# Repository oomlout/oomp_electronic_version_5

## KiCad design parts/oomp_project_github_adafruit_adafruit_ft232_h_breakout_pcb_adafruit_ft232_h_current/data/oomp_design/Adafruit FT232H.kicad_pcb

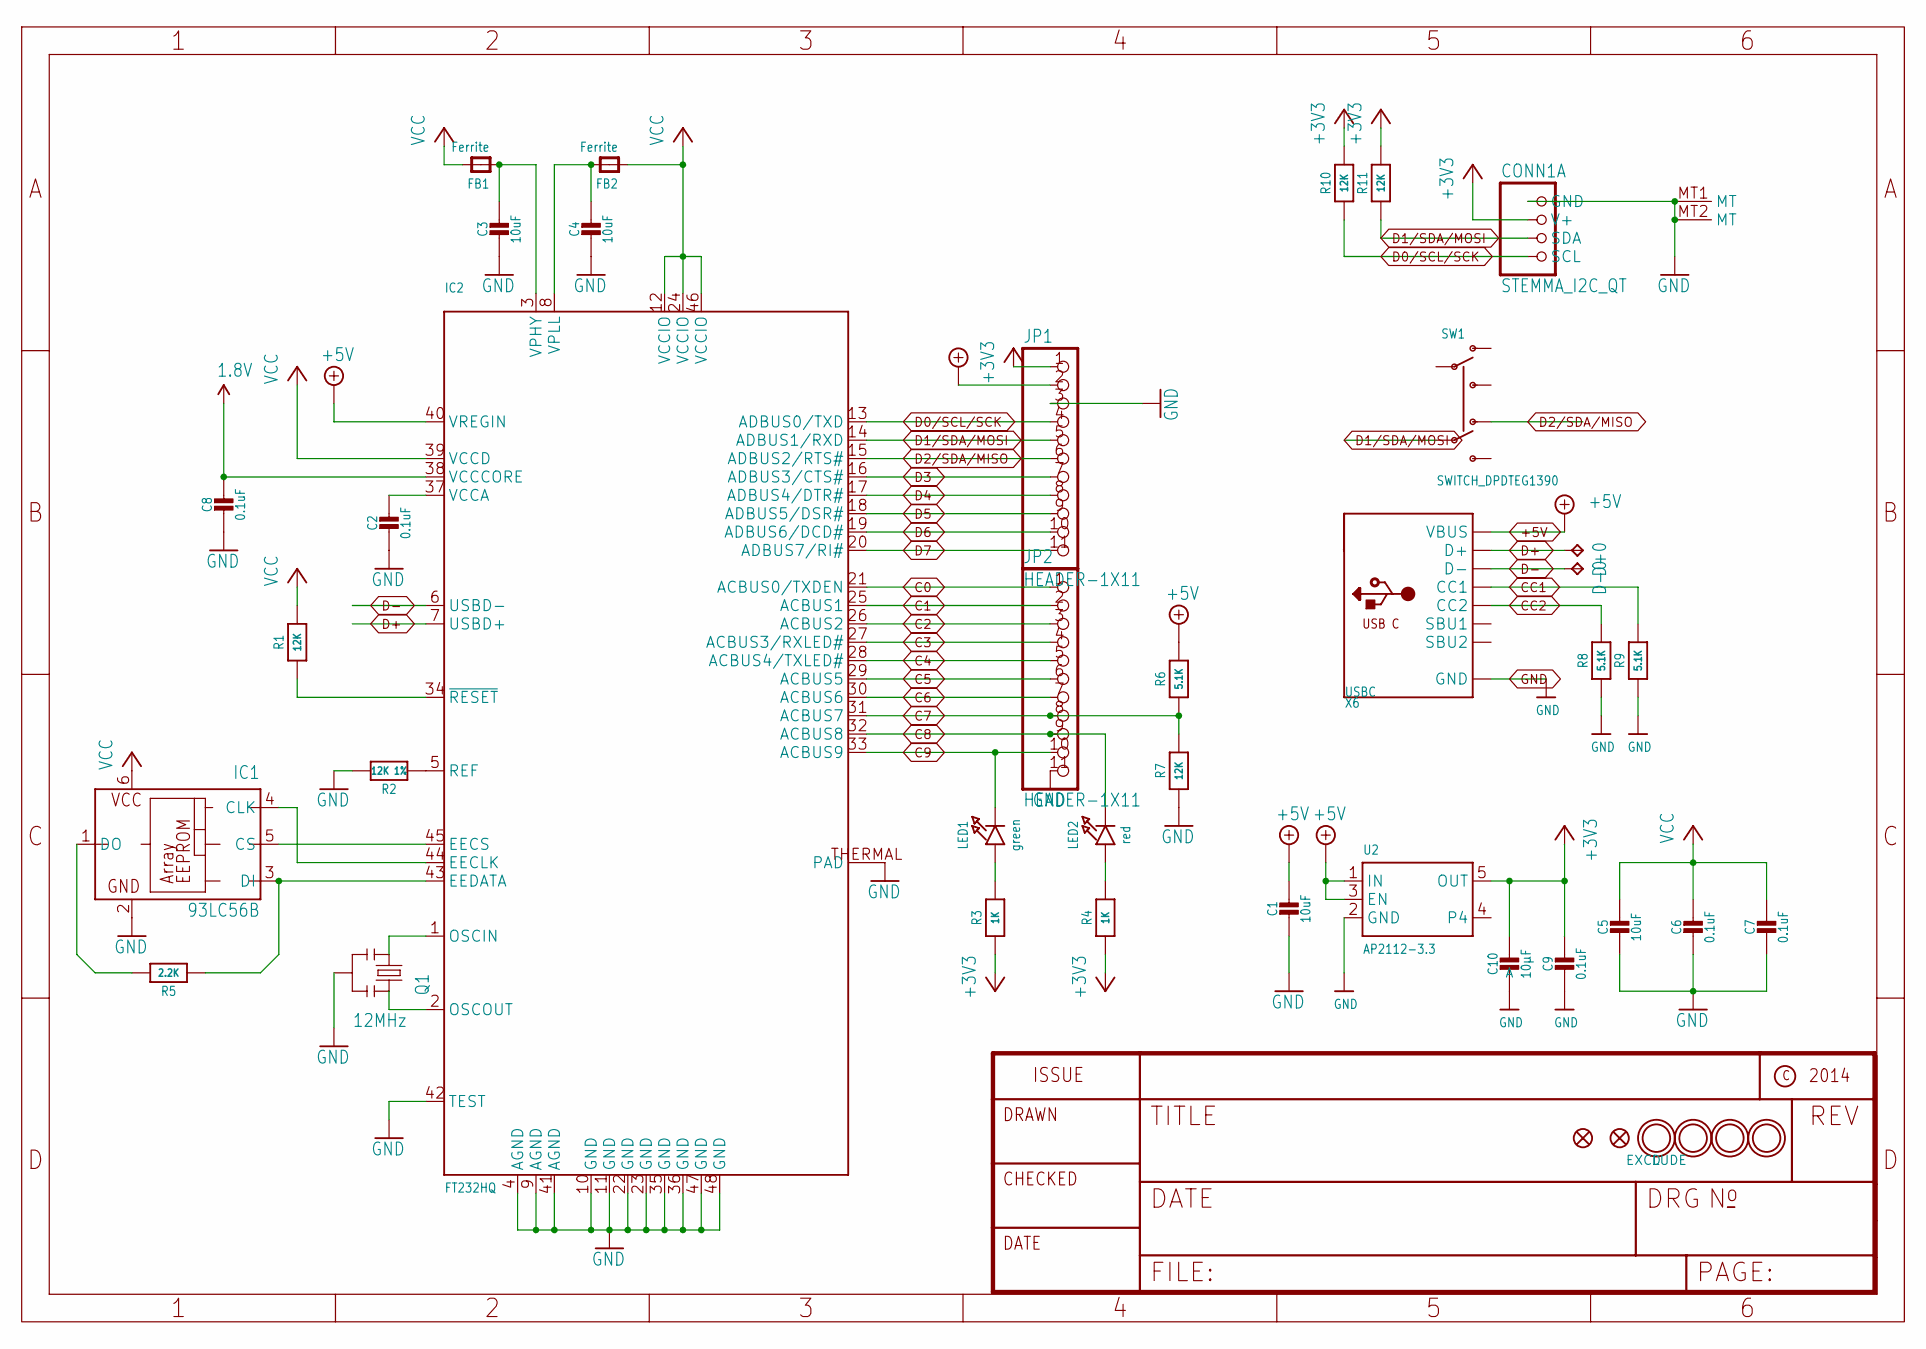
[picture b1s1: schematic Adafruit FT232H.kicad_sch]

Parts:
C1, C3, C4, C5: 10uF; 0805-NO
C2, C6, C7, C8, C9: 0.1uF; 0603-NO
C10: 10µF; 0805-NO
CONN1: STEMMA_I2C_QT; JST_SH4
D+0: TPTP17R; TP17R
D-0: TPTP17R; TP17R
FB1, FB2: Ferrite; _0805
FID1, FID2: FIDUCIAL""; FIDUCIAL_1MM
IC1: 93LC56B; SOT23-6; MPN 93LC76AT-I/OT
IC2: FT232HQ; QFN48_8MM
JP1, JP2: HEADER-1X11; 1X11_ROUND
LED1: green; CHIPLED_0805_NOOUTLINE
LED2: red; CHIPLED_0805_NOOUTLINE
Q1: 12MHz; RESONATOR-SMD
R1, R7, R10, R11: 12K; 0603-NO
R2: 12K 1%; 0603-NO
R3, R4: 1K; 0603-NO
R5: 2.2K; 0603-NO
R6, R8, R9: 5.1K; 0603-NO
SW1: SWITCH_DPDTEG1390; EG1390
U2: AP2112-3.3; SOT23-5
U$4, U$5, U$6, U$7: MOUNTINGHOLE2.5; MOUNTINGHOLE_2.5_PLATED
X6: USBC; USB_C_CUSB31-CFM2AX-01-X

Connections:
1.8V: C8.1, IC2.38 (VCCCORE)
+3V3: C9.1, C10.1, CONN1.2 (V+), JP1.1, R3.1, R4.1, R10.2, R11.2, U2.5 (OUT)
+5V: C1.1, IC2.40 (VREGIN), JP1.2, R6.2, U2.1 (IN), U2.3 (EN), X6.A4B9 (VBUS), X6.B4A9 (VBUS)
C0: IC2.21 (ACBUS0/TXDEN), JP2.1
C1: IC2.25 (ACBUS1), JP2.2
C2: IC2.26 (ACBUS2), JP2.3
C3: IC2.27 (ACBUS3/RXLED#), JP2.4
C4: IC2.28 (ACBUS4/TXLED#), JP2.5
C5: IC2.29 (ACBUS5), JP2.6
C6: IC2.30 (ACBUS6), JP2.7
C7: IC2.31 (ACBUS7), JP2.8, R6.1, R7.2
C8: IC2.32 (ACBUS8), JP2.9, LED2.C
C9: IC2.33 (ACBUS9), JP2.10, LED1.C
CC1: R9.2, X6.A5 (CC1)
CC2: R8.2, X6.B5 (CC2)
D0/SCL/SCK: CONN1.4 (SCL), IC2.13 (ADBUS0/TXD), JP1.4, R10.1
D1/SDA/MOSI: CONN1.3 (SDA), IC2.14 (ADBUS1/RXD), JP1.5, R11.1, SW1.P2
D2/SDA/MISO: IC2.15 (ADBUS2/RTS#), JP1.6, SW1.O2
D3: IC2.16 (ADBUS3/CTS#), JP1.7
D4: IC2.17 (ADBUS4/DTR#), JP1.8
D5: IC2.18 (ADBUS5/DSR#), JP1.9
D6: IC2.19 (ADBUS6/DCD#), JP1.10
D7: IC2.20 (ADBUS7/RI#), JP1.11
D+: D+0.TP, IC2.7 (USBD+), X6.A6 (D+), X6.B6 (D+)
D-: D-0.TP, IC2.6 (USBD-), X6.A7 (D-), X6.B7 (D-)
GND: C1.2, C2.2, C3.2, C4.2, C5.2, C6.2, C7.2, C8.2, C9.2, C10.2, CONN1.1 (GND), CONN1.MT1 (MT), CONN1.MT2 (MT), IC1.2 (GND), IC2.4 (AGND), IC2.9 (AGND), IC2.10 (GND), IC2.11 (GND), IC2.22 (GND), IC2.23 (GND), IC2.35 (GND), IC2.36 (GND), IC2.41 (AGND), IC2.42 (TEST), IC2.47 (GND), IC2.48 (GND), IC2.THERMAL (PAD), JP1.3, JP2.11, Q1.2, R2.2, R7.1, R8.1, R9.1, U2.2 (GND), X6.A1B12 (GND), X6.B1A12 (GND)
unnamed: IC2.1 (OSCIN), Q1.1
unnamed: IC2.2 (OSCOUT), Q1.3
unnamed: IC2.5 (REF), R2.1
unnamed: LED2.A, R4.2
unnamed: IC2.34 (~RESET), R1.1
unnamed: LED1.A, R3.2
unnamed: IC1.3 (DI), IC2.43 (EEDATA), R5.1
unnamed: IC1.5 (CS), IC2.45 (EECS)
unnamed: IC1.4 (CLK), IC2.44 (EECLK)
unnamed: IC1.1 (DO), R5.2
VCC: C5.1, C6.1, C7.1, FB1.2, FB2.1, IC1.6 (VCC), IC2.12 (VCCIO), IC2.24 (VCCIO), IC2.39 (VCCD), IC2.46 (VCCIO), R1.2
VCCA: C2.1, IC2.37 (VCCA)
VPHY: C3.1, FB1.1, IC2.3 (VPHY)
VPLL: C4.1, FB2.2, IC2.8 (VPLL)

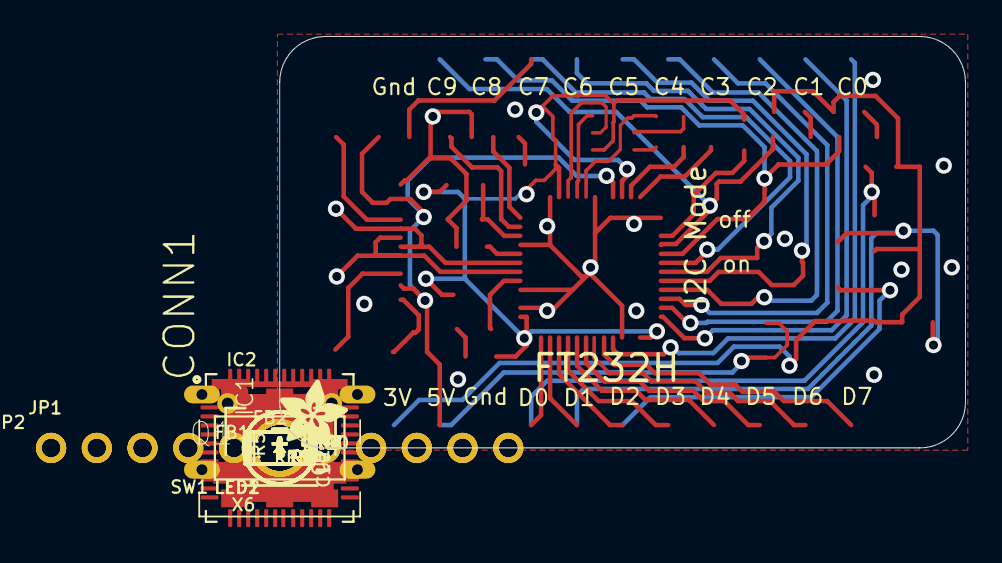
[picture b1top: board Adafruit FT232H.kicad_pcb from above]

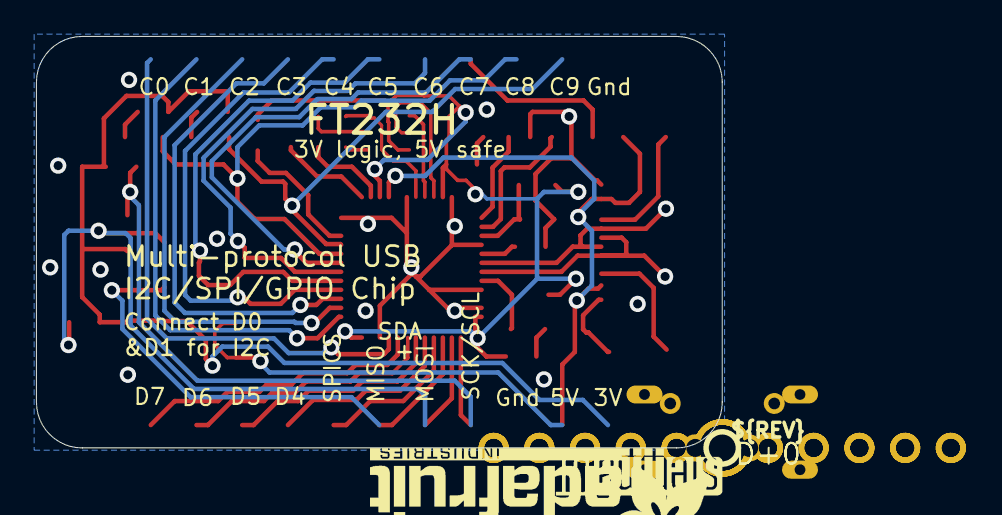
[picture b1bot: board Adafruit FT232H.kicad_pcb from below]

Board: 2 copper layers, 38.1 x 22.9 mm, 46 parts (5 on the bottom side), 40 nets.

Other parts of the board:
U$2: ADAFRUIT_3.5MM
U$3: ADAFRUIT_TEXT_20MM
U$8: STEMMAQT
U$11: PCBFEAT-REV-040

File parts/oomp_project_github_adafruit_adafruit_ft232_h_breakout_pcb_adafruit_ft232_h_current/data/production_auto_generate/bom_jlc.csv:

Comment,Designator,Footprint,LCSC Part #
,"JP1,JP2",Adafruit FT232H-import-fps:1X11_ROUND,C2894934
,U$2,Adafruit FT232H-import-fps:ADAFRUIT_3.5MM,
,U$3,Adafruit FT232H-import-fps:ADAFRUIT_TEXT_20MM,
,SW1,Adafruit FT232H-import-fps:EG1390,
,U$11,Adafruit FT232H-import-fps:PCBFEAT-REV-040,
,U$8,Adafruit FT232H-import-fps:STEMMAQT,
0.1uF,"C2,C6,C7,C8,C9",Adafruit FT232H-import-fps:0603-NO,C14663
10uF,"C1,C3,C4,C5",Adafruit FT232H-import-fps:0805-NO,
10µF,C10,Adafruit FT232H-import-fps:0805-NO,
12K,"R1,R7,R10,R11",Adafruit FT232H-import-fps:0603-NO,C2906989
12K 1%,R2,Adafruit FT232H-import-fps:0603-NO,C2906989
12MHz,Q1,Adafruit FT232H-import-fps:RESONATOR-SMD,
1K,"R3,R4",Adafruit FT232H-import-fps:0603-NO,C2907002
2.2K,R5,Adafruit FT232H-import-fps:0603-NO,C4190
5.1K,"R6,R8,R9",Adafruit FT232H-import-fps:0603-NO,C23186
93LC56B,IC1,Adafruit FT232H-import-fps:SOT23-6,
AP2112-3.3,U2,Adafruit FT232H-import-fps:SOT23-5,
Ferrite,"FB1,FB2",Adafruit FT232H-import-fps:_0805,
FT232HQ,IC2,Adafruit FT232H-import-fps:QFN48_8MM,
green,LED1,Adafruit FT232H-import-fps:CHIPLED_0805_NOOUTLINE,
red,LED2,Adafruit FT232H-import-fps:CHIPLED_0805_NOOUTLINE,
STEMMA_I2C_QT,CONN1,Adafruit FT232H-import-fps:JST_SH4,C160404
TPTP17R,"D+0,D-0",Adafruit FT232H-import-fps:TP17R,
USBC,X6,Adafruit FT232H-import-fps:USB_C_CUSB31-CFM2AX-01-X,

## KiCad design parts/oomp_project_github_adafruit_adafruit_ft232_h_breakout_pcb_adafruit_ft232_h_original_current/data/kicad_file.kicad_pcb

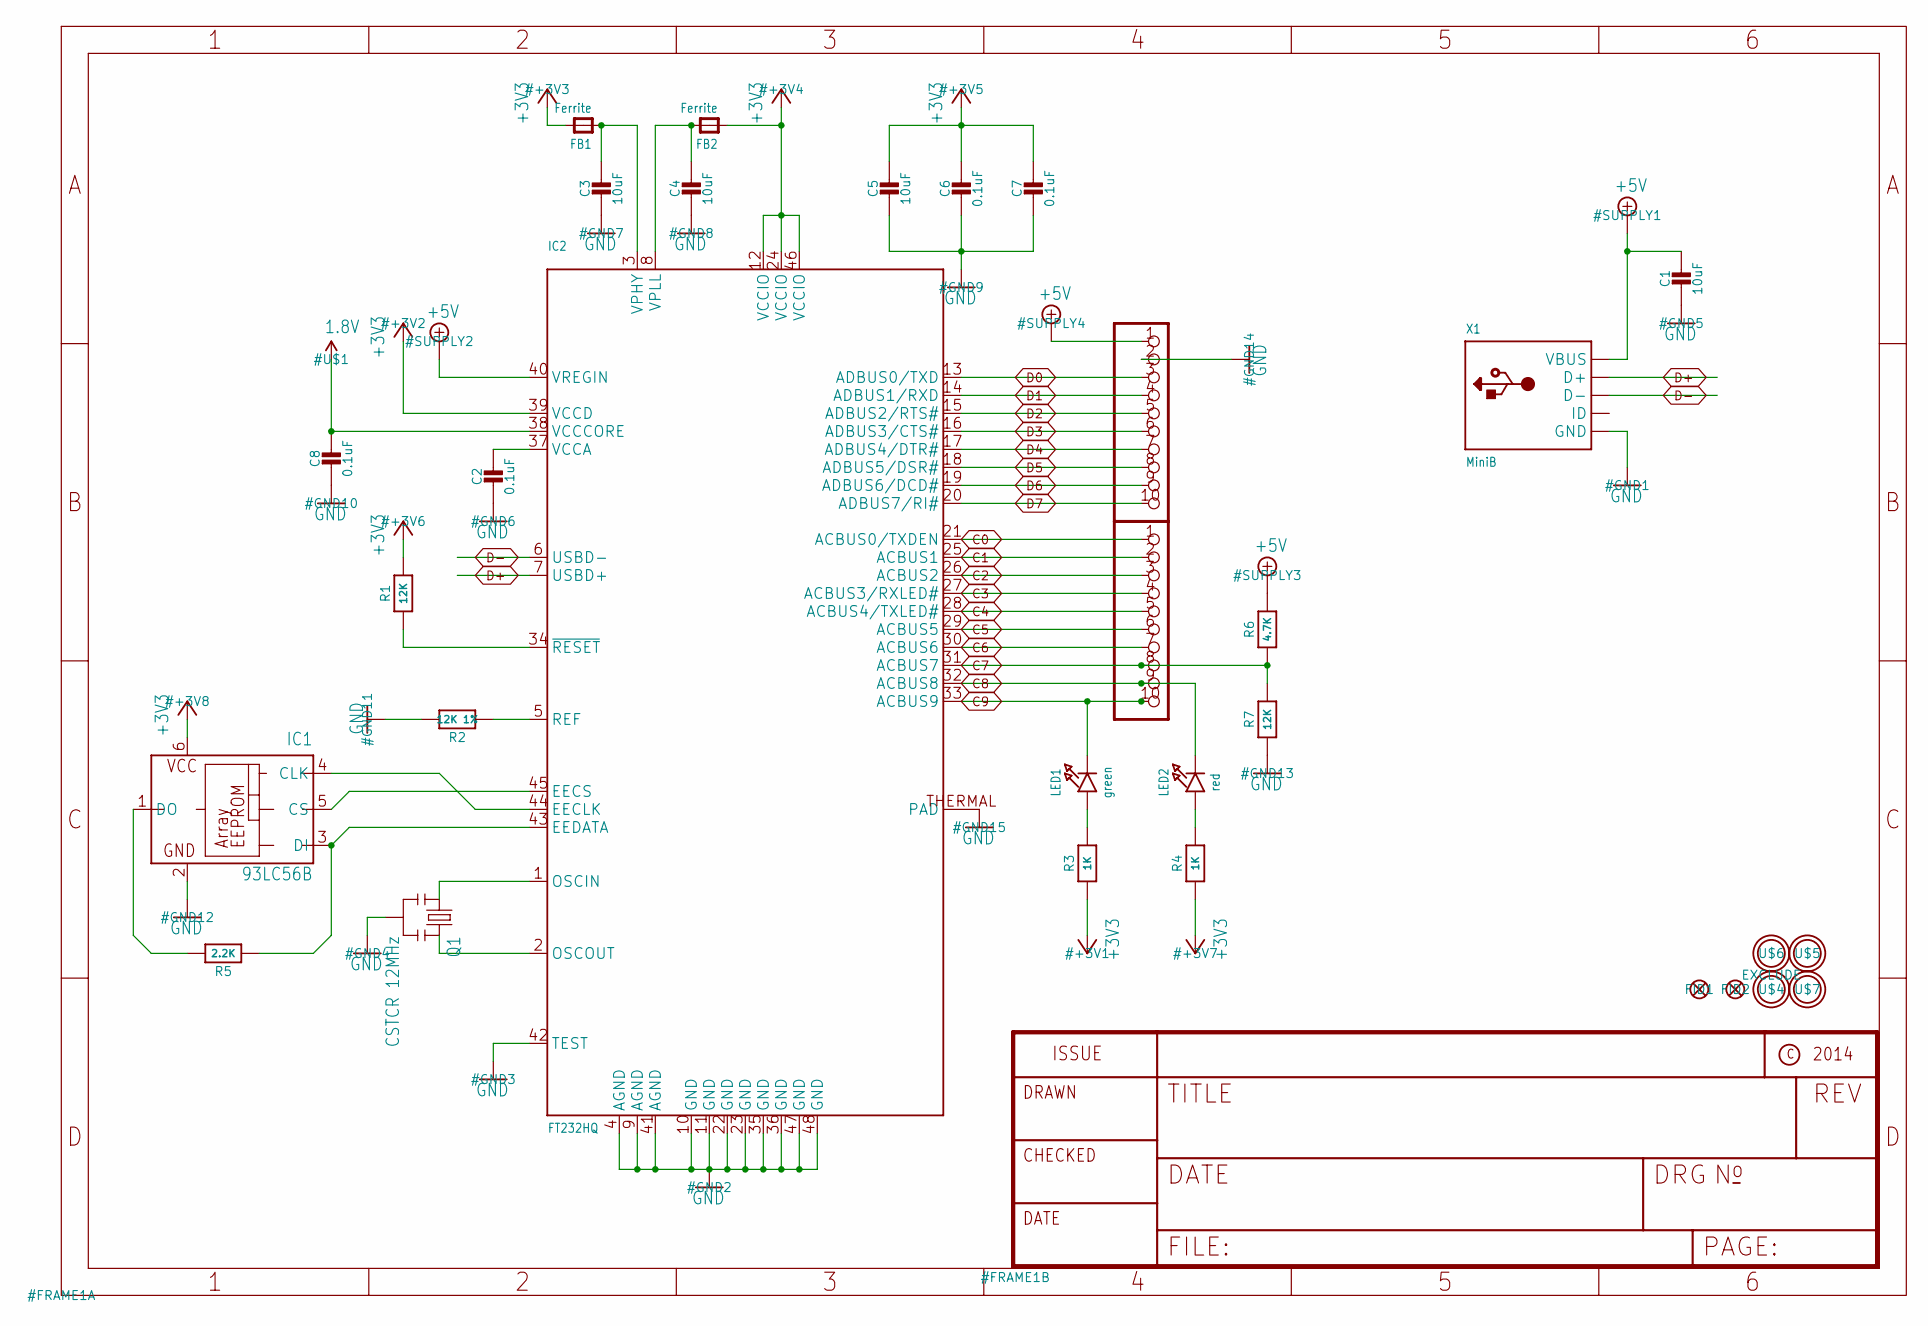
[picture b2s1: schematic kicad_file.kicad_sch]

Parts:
C1, C3, C4, C5: 10uF; 0805-NO
C2, C6, C7, C8: 0.1uF; 0805-NO
FB1, FB2: Ferrite; _0805
FID1, FID2: FIDUCIAL""; FIDUCIAL_1MM
IC1: 93LC56B; SOT23-6; MPN 93LC76AT-I/OT
IC2: FT232HQ; QFN48_8MM
LED1: green; CHIPLED_0805_NOOUTLINE
LED2: red; CHIPLED_0805_NOOUTLINE
Q1: CSTCR 12MHz; RESONATOR-SMD
R1, R7: 12K; 0805-NO
R2: 12K 1%; 0805-NO
R3, R4: 1K; 0805-NO
R5: 2.2K; _0805MP
R6: 4.7K; 0805-NO
U$2, U$3: PINHD-1X10; 1X10-BIG
U$4, U$5, U$6, U$7: MOUNTINGHOLE2.5; MOUNTINGHOLE_2.5_PLATED
X1: MiniB; 4UCONN_20329

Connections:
1.8V: C8.1, IC2.38 (VCCCORE)
+3V3: C5.1, C6.1, C7.1, FB1.2, FB2.1, IC1.6 (VCC), IC2.12 (VCCIO), IC2.24 (VCCIO), IC2.39 (VCCD), IC2.46 (VCCIO), R1.2, R3.1, R4.1
+5V: C1.1, IC2.40 (VREGIN), R6.2, U$2.1, X1.VBUS
C0: IC2.21 (ACBUS0/TXDEN), U$3.1
C1: IC2.25 (ACBUS1), U$3.2
C2: IC2.26 (ACBUS2), U$3.3
C3: IC2.27 (ACBUS3/RXLED#), U$3.4
C4: IC2.28 (ACBUS4/TXLED#), U$3.5
C5: IC2.29 (ACBUS5), U$3.6
C6: IC2.30 (ACBUS6), U$3.7
C7: IC2.31 (ACBUS7), R6.1, R7.2, U$3.8
C8: IC2.32 (ACBUS8), LED2.C, U$3.9
C9: IC2.33 (ACBUS9), LED1.C, U$3.10
D0: IC2.13 (ADBUS0/TXD), U$2.3
D1: IC2.14 (ADBUS1/RXD), U$2.4
D2: IC2.15 (ADBUS2/RTS#), U$2.5
D3: IC2.16 (ADBUS3/CTS#), U$2.6
D4: IC2.17 (ADBUS4/DTR#), U$2.7
D5: IC2.18 (ADBUS5/DSR#), U$2.8
D6: IC2.19 (ADBUS6/DCD#), U$2.9
D7: IC2.20 (ADBUS7/RI#), U$2.10
D+: IC2.7 (USBD+), X1.D+
D-: IC2.6 (USBD-), X1.D-
GND: C1.2, C2.2, C3.2, C4.2, C5.2, C6.2, C7.2, C8.2, IC1.2 (GND), IC2.4 (AGND), IC2.9 (AGND), IC2.10 (GND), IC2.11 (GND), IC2.22 (GND), IC2.23 (GND), IC2.35 (GND), IC2.36 (GND), IC2.41 (AGND), IC2.42 (TEST), IC2.47 (GND), IC2.48 (GND), IC2.THERMAL (PAD), Q1.2, R2.2, R7.1, U$2.2, X1.BASE@1 (GND), X1.BASE@2 (GND), X1.GND, X1.SPRT@1 (GND), X1.SPRT@2 (GND), X1.SPRT@3 (GND), X1.SPRT@4 (GND)
unnamed: IC2.1 (OSCIN), Q1.1
unnamed: IC2.2 (OSCOUT), Q1.3
unnamed: IC2.5 (REF), R2.1
unnamed: LED2.A, R4.2
unnamed: IC2.34 (~RESET), R1.1
unnamed: LED1.A, R3.2
unnamed: IC1.3 (DI), IC2.43 (EEDATA), R5.1
unnamed: IC1.5 (CS), IC2.45 (EECS)
unnamed: IC1.4 (CLK), IC2.44 (EECLK)
unnamed: IC1.1 (DO), R5.2
VCCA: C2.1, IC2.37 (VCCA)
VPHY: C3.1, FB1.1, IC2.3 (VPHY)
VPLL: C4.1, FB2.2, IC2.8 (VPLL)

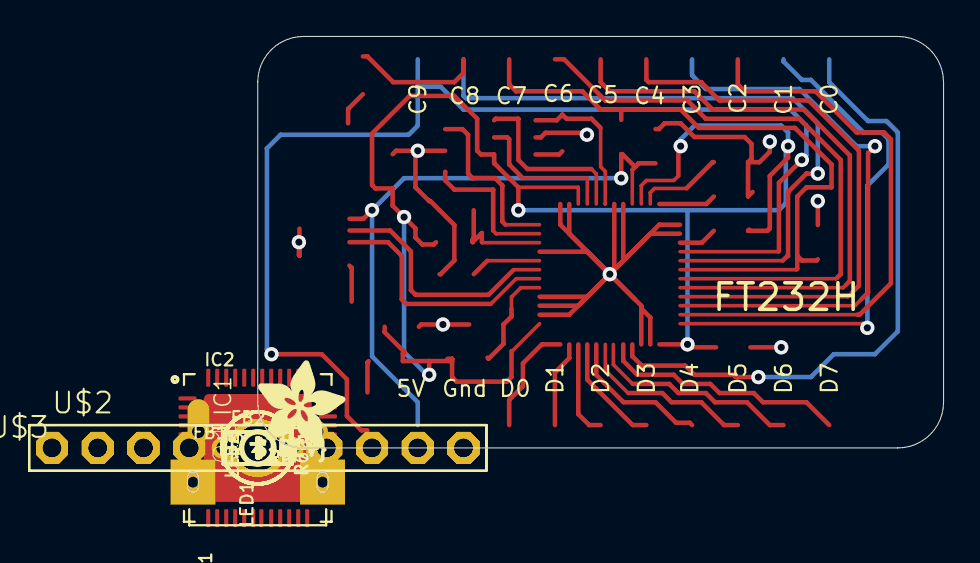
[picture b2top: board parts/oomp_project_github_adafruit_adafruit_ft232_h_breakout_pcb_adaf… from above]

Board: 2 copper layers, 38.1 x 22.9 mm, 34 parts (1 on the bottom side), 37 nets.

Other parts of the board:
U$8: ADAFRUIT_5MM
U$9: ADAFRUIT_TEXT_30MM
U$11: PCBFEAT-REV-040

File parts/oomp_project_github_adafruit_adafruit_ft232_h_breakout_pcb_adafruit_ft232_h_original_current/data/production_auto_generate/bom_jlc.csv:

Comment,Designator,Footprint,LCSC Part #
,U$8,Adafruit FT232H Original-import-fps:ADAFRUIT_5MM,
,U$9,Adafruit FT232H Original-import-fps:ADAFRUIT_TEXT_30MM,
,U$11,Adafruit FT232H Original-import-fps:PCBFEAT-REV-040,
0.1uF,"C2,C6,C7,C8",Adafruit FT232H Original-import-fps:0805-NO,
10uF,"C1,C3,C4,C5",Adafruit FT232H Original-import-fps:0805-NO,
12K,"R1,R7",Adafruit FT232H Original-import-fps:0805-NO,C2907225
12K 1%,R2,Adafruit FT232H Original-import-fps:0805-NO,C2907225
1K,"R3,R4",Adafruit FT232H Original-import-fps:0805-NO,C17513
2.2K,R5,Adafruit FT232H Original-import-fps:_0805MP,C17520
4.7K,R6,Adafruit FT232H Original-import-fps:0805-NO,C2907264
93LC56B,IC1,Adafruit FT232H Original-import-fps:SOT23-6,
CSTCR 12MHz,Q1,Adafruit FT232H Original-import-fps:RESONATOR-SMD,
Ferrite,"FB1,FB2",Adafruit FT232H Original-import-fps:_0805,
FT232HQ,IC2,Adafruit FT232H Original-import-fps:QFN48_8MM,
green,LED1,Adafruit FT232H Original-import-fps:CHIPLED_0805_NOOUTLINE,
MiniB,X1,Adafruit FT232H Original-import-fps:4UCONN_20329,
PINHD-1X10,"U$2,U$3",Adafruit FT232H Original-import-fps:1X10-BIG,
red,LED2,Adafruit FT232H Original-import-fps:CHIPLED_0805_NOOUTLINE,

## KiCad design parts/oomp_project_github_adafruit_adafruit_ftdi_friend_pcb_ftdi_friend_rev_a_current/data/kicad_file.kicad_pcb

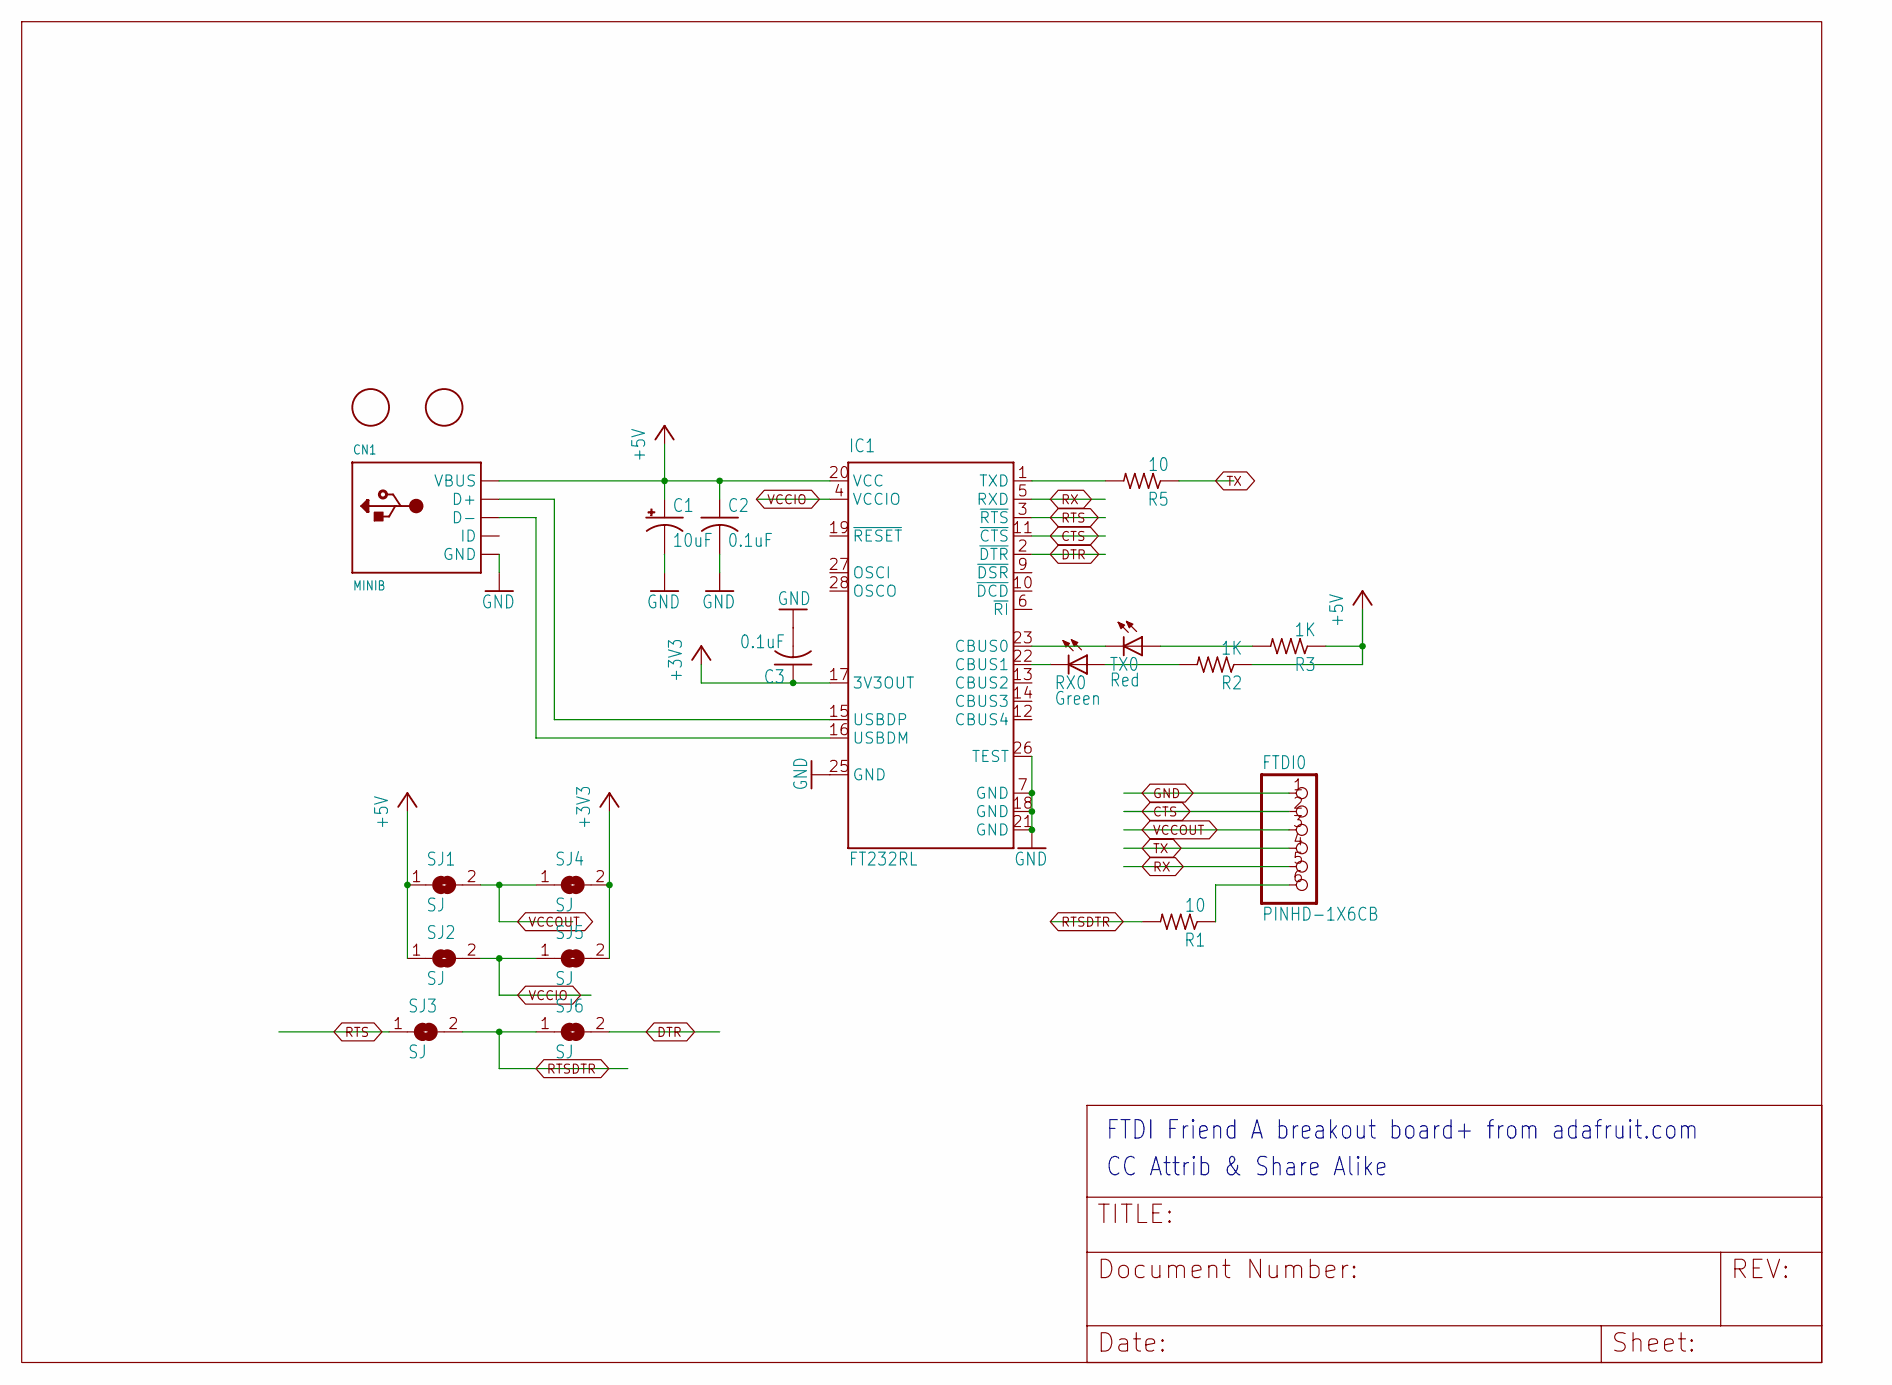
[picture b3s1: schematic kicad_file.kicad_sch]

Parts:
C1: 10uF; A_3216-18R
C2, C3: 0.1uF; C0805K
CN1: MINIB; USB-MINIB
FTDI0: PINHD-1X6CB; 1X06-CLEANBIG
IC1: FT232RL; SSOP28
R1, R5: 10; R0805
R2, R3: 1K; R0805
RX0: Green; CHIP-LED0805
SJ1, SJ2, SJ3, SJ4, SJ5, SJ6: SJ
TX0: Red; CHIP-LED0805
U$1, U$2: FIDUCIAL; FIDUCIAL_1MM

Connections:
+3V3: C3.1, IC1.17 (3V3OUT), SJ4.2, SJ5.2
+5V: C1.+, C2.1, CN1.VBUS, IC1.20 (VCC), R2.1, R3.1, SJ1.1, SJ2.1
CTS: FTDI0.2, IC1.11 (~CTS)
DTR: IC1.2 (~DTR), SJ6.2
GND: C1.-, C2.2, C3.2, CN1.GND, FTDI0.1, IC1.7 (GND), IC1.18 (GND), IC1.21 (GND), IC1.25 (GND), IC1.26 (TEST)
unnamed: FTDI0.6, R1.1
unnamed: CN1.D+, IC1.15 (USBDP)
unnamed: CN1.D-, IC1.16 (USBDM)
unnamed: IC1.1 (TXD), R5.2
unnamed: IC1.23 (CBUS0), TX0.C
unnamed: IC1.22 (CBUS1), RX0.C
unnamed: R2.2, RX0.A
unnamed: R3.2, TX0.A
RTS: IC1.3 (~RTS), SJ3.1
RTSDTR: R1.2, SJ3.2, SJ6.1
RX: FTDI0.5, IC1.5 (RXD)
TX: FTDI0.4, R5.1
VCCIO: IC1.4 (VCCIO), SJ2.2, SJ5.1
VCCOUT: FTDI0.3, SJ1.2, SJ4.1

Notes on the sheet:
CC Attrib & Share Alike
FTDI Friend~{} A breakout board+ from adafruit.com

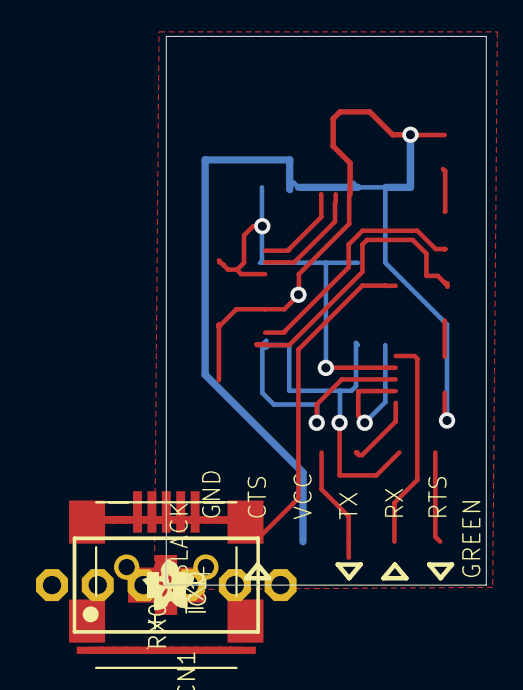
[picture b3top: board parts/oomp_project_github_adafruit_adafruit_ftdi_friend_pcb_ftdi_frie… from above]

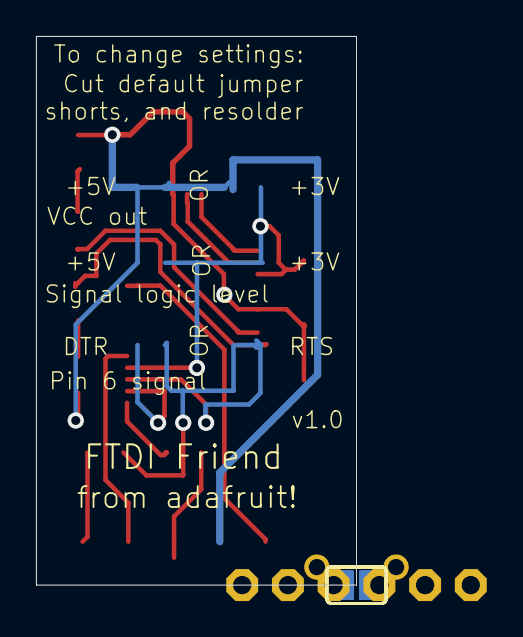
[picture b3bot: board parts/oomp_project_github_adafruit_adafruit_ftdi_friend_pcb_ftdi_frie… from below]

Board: 16 copper layers, 17.8 x 30.5 mm, 21 parts (6 on the bottom side), 19 nets.

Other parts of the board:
U$3: ADAFRUIT200MIL
